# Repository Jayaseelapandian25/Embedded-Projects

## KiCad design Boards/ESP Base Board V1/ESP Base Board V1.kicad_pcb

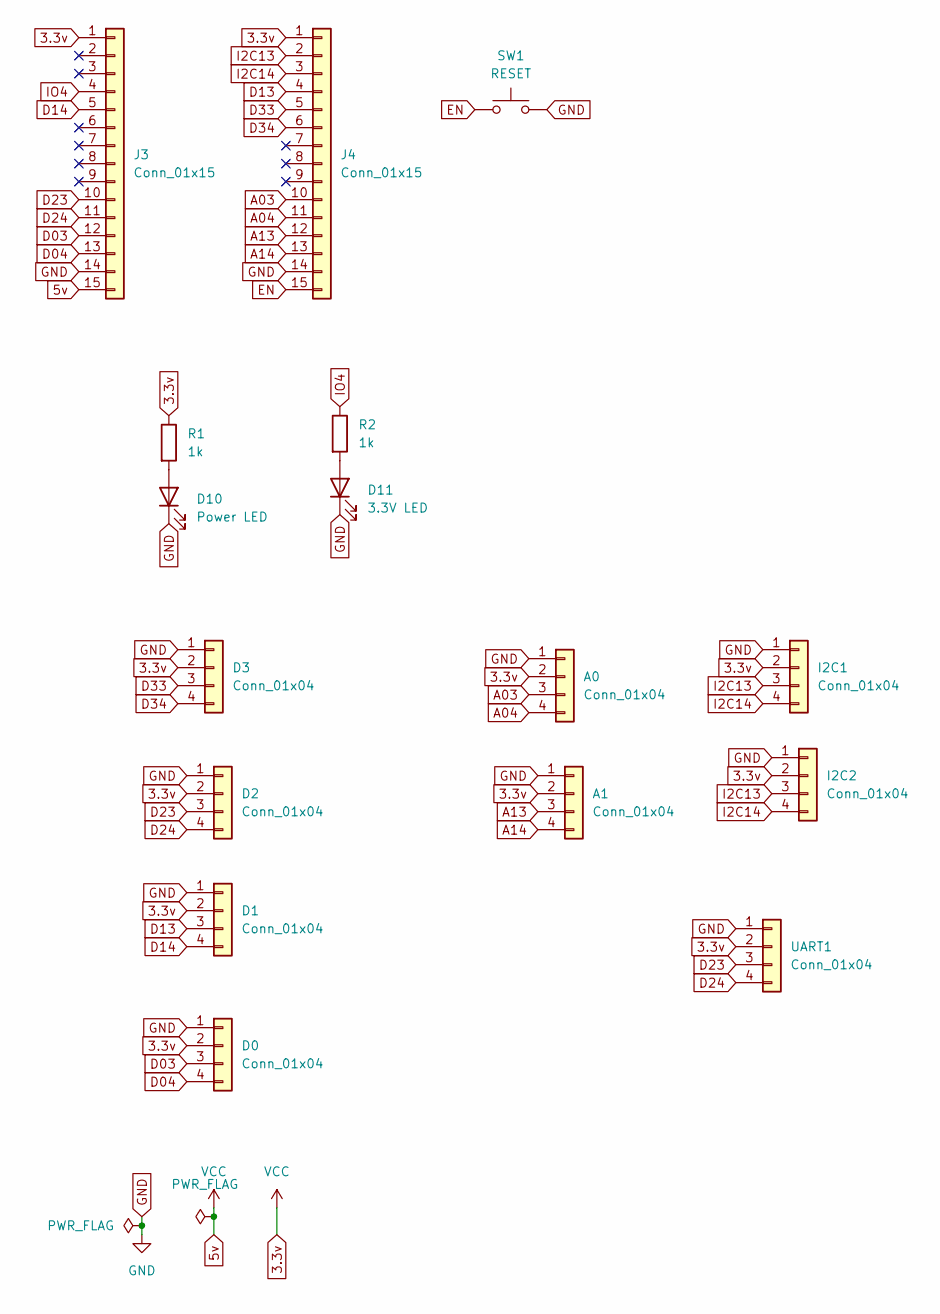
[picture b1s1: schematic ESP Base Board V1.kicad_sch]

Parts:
A0, A1: Conn_01x04; PinHeader_1x04_P2.54mm_Vertical
D0, D1, D2, D3: Conn_01x04; PinHeader_1x04_P2.54mm_Vertical
D10: Power LED; LED_0805_2012Metric_Pad1.15x1.40mm_HandSolder
D11: 3.3V LED; LED_0805_2012Metric_Pad1.15x1.40mm_HandSolder
I2C1, I2C2: Conn_01x04; PinHeader_1x04_P2.54mm_Vertical
J3, J4: Conn_01x15; PinSocket_1x15_P2.54mm_Vertical
R1, R2: 1k; R_0805_2012Metric_Pad1.20x1.40mm_HandSolder
SW1: RESET; SW_SPST_TL3342
UART1: Conn_01x04; PinHeader_1x04_P2.54mm_Vertical

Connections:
3.3v: A0.2, A1.2, D0.2, D1.2, D2.2, D3.2, I2C1.2, I2C2.2, J3.1, J3.15, J4.1, R1.1, UART1.2
A03: A0.3, J4.10
A04: A0.4, J4.11
A13: A1.3, J4.12
A14: A1.4, J4.13
D03: D0.3, J3.12
D04: D0.4, J3.13
D13: D1.3, J4.4
D14: D1.4, J3.5
D23: D2.3, J3.10, UART1.3
D24: D2.4, J3.11, UART1.4
D33: D3.3, J4.5
D34: D3.4, J4.6
EN: J4.15, SW1.1
GND: A0.1, A1.1, D0.1, D1.1, D2.1, D3.1, D10.1 (K), D11.1 (K), I2C1.1, I2C2.1, J3.14, J4.14, SW1.2, UART1.1
I2C13: I2C1.3, I2C2.3, J4.2
I2C14: I2C1.4, I2C2.4, J4.3
IO4: J3.4, R2.1
unnamed: D10.2 (A), R1.2
unnamed: D11.2 (A), R2.2

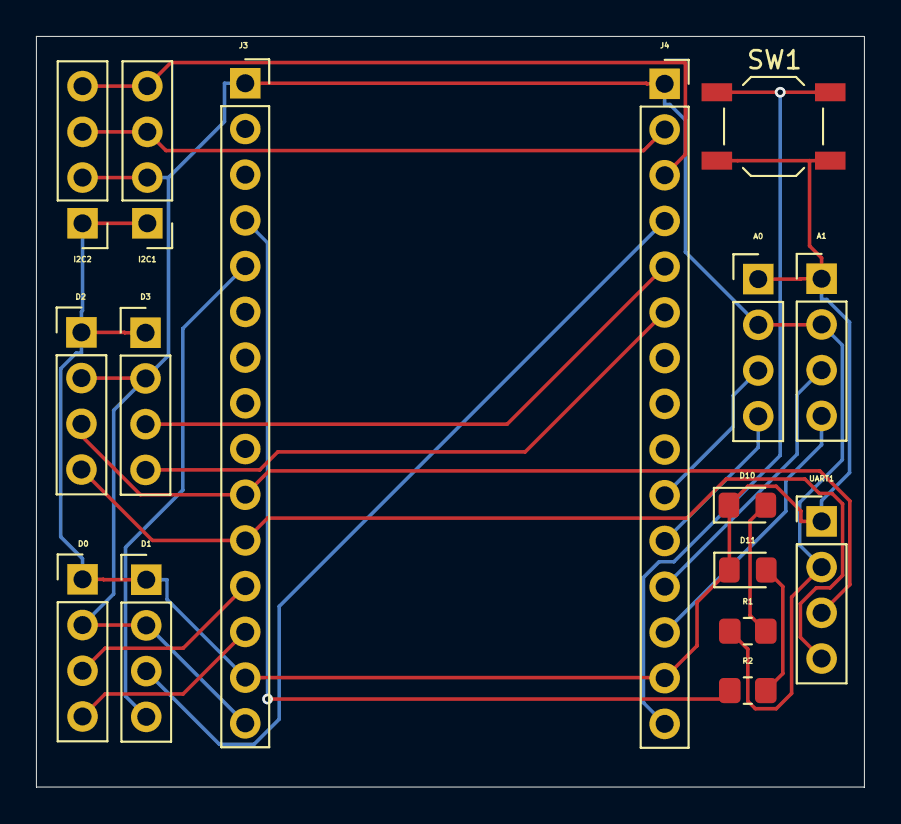
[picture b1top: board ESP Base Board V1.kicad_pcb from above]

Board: 2 copper layers, 46.0 x 41.7 mm, 16 parts (0 on the bottom side), 20 nets.

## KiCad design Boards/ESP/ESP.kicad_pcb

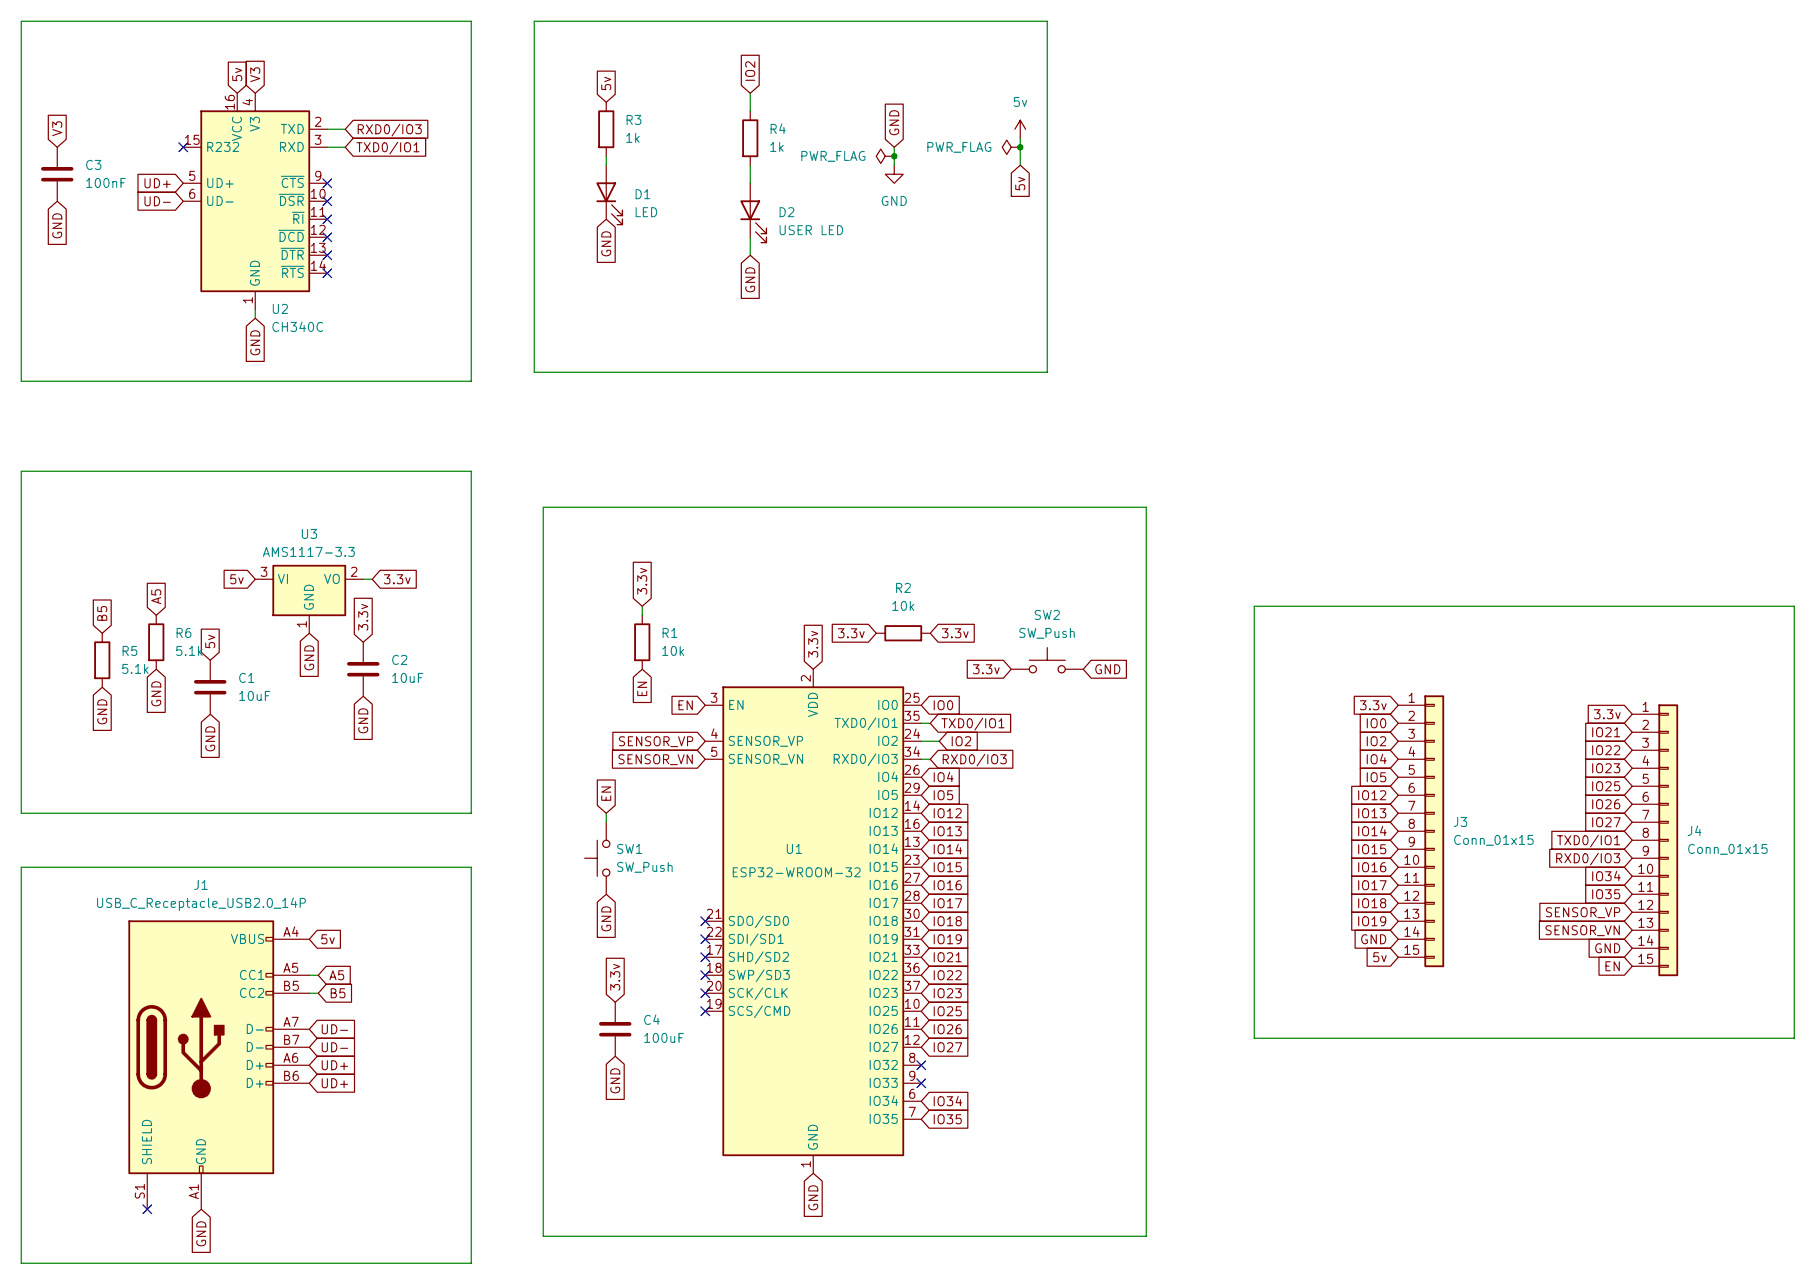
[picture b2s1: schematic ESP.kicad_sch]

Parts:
C1, C2: 10uF; C_0805_2012Metric
C3: 100nF; C_0805_2012Metric
C4: 100uF; C_0805_2012Metric
D1: LED; LED_0805_2012Metric
D2: USER LED; LED_0805_2012Metric
J1: USB_C_Receptacle_USB2.0_14P; USB_C_Receptacle_HRO_TYPE-C-31-M-12
J3, J4: Conn_01x15; PinHeader_1x15_P2.54mm_Vertical
R1, R2: 10k; R_0805_2012Metric
R3, R4: 1k; R_0805_2012Metric
R5, R6: 5.1k; R_0805_2012Metric
SW1, SW2: SW_Push; SW_SPST_TL3342
U1: ESP32-WROOM-32
U2: CH340C; SOIC-16_3.9x9.9mm_P1.27mm
U3: AMS1117-3.3; SOT-223-3_TabPin2

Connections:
3.3v: C2.1, C4.1, J3.1, J4.1, R1.1, R2.1, R2.2, SW2.1, U1.2 (VDD), U3.2 (VO)
5v: C1.1, J1.A4 (VBUS), J1.A9 (VBUS), J1.B4 (VBUS), J1.B9 (VBUS), J3.15, R3.1, U2.16 (VCC), U3.3 (VI)
A5: J1.A5 (CC1), R6.1
B5: J1.B5 (CC2), R5.1
EN: J4.15, R1.2, SW1.2, U1.3 (EN)
GND: C1.2, C2.2, C3.2, C4.2, D1.1 (K), D2.1 (K), J1.A1 (GND), J1.A12 (GND), J1.B1 (GND), J1.B12 (GND), J3.14, J4.14, R5.2, R6.2, SW1.1, SW2.2, U1.1 (GND), U1.15 (GND), U1.38 (GND), U1.39 (GND), U2.1 (GND), U3.1 (GND)
IO0: J3.2, U1.25 (IO0)
IO2: J3.3, R4.1, U1.24 (IO2)
IO4: J3.4, U1.26 (IO4)
IO5: J3.5, U1.29 (IO5)
IO12: J3.6, U1.14 (IO12)
IO13: J3.7, U1.16 (IO13)
IO14: J3.8, U1.13 (IO14)
IO15: J3.9, U1.23 (IO15)
IO16: J3.10, U1.27 (IO16)
IO17: J3.11, U1.28 (IO17)
IO18: J3.12, U1.30 (IO18)
IO19: J3.13, U1.31 (IO19)
IO21: J4.2, U1.33 (IO21)
IO22: J4.3, U1.36 (IO22)
IO23: J4.4, U1.37 (IO23)
IO25: J4.5, U1.10 (IO25)
IO26: J4.6, U1.11 (IO26)
IO27: J4.7, U1.12 (IO27)
IO34: J4.10, U1.6 (IO34)
IO35: J4.11, U1.7 (IO35)
unnamed: D1.2 (A), R3.2
unnamed: D2.2 (A), R4.2
RXD0/IO3: J4.9, U1.34 (RXD0/IO3), U2.2 (TXD)
SENSOR_VN: J4.13, U1.5 (SENSOR_VN)
SENSOR_VP: J4.12, U1.4 (SENSOR_VP)
TXD0/IO1: J4.8, U1.35 (TXD0/IO1), U2.3 (RXD)
UD+: J1.A6 (D+), J1.B6 (D+), U2.5 (UD+)
UD-: J1.A7 (D-), J1.B7 (D-), U2.6 (UD-)
V3: C3.1, U2.4 (V3)

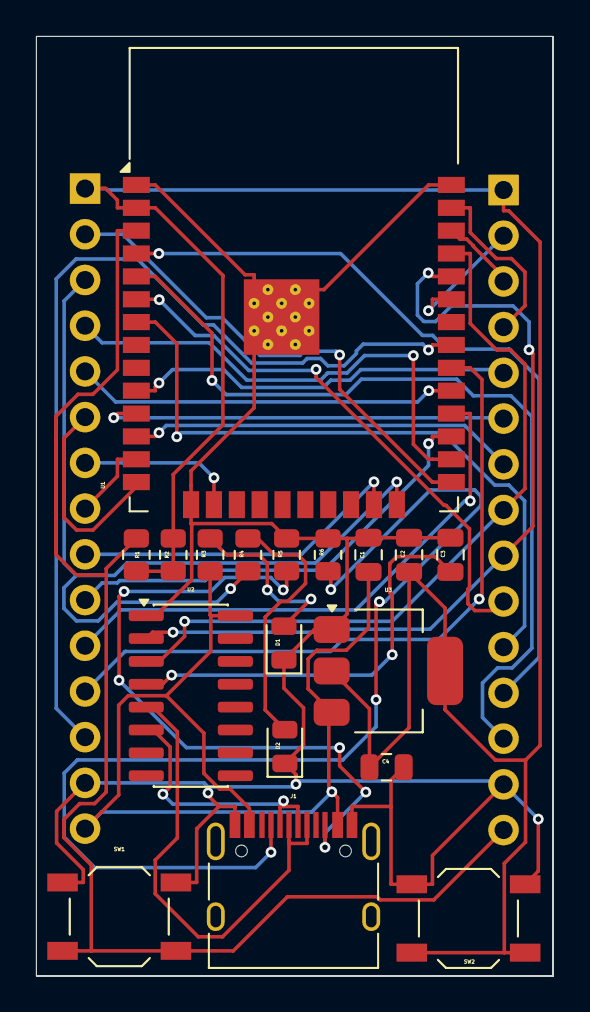
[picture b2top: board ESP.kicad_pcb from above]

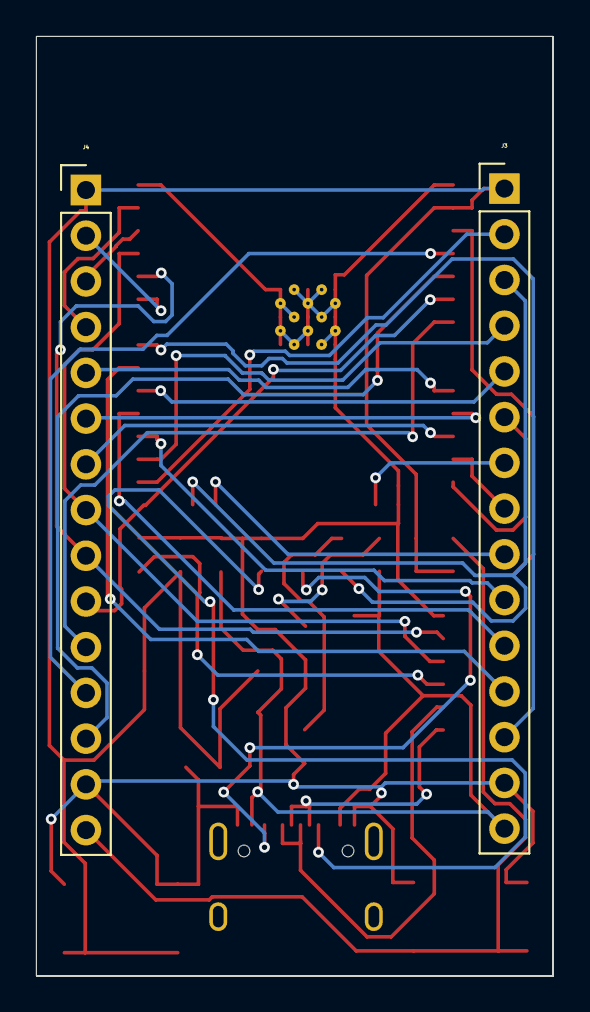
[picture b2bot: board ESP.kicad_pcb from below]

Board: 2 copper layers, 28.7 x 52.2 mm, 20 parts (2 on the bottom side), 35 nets.

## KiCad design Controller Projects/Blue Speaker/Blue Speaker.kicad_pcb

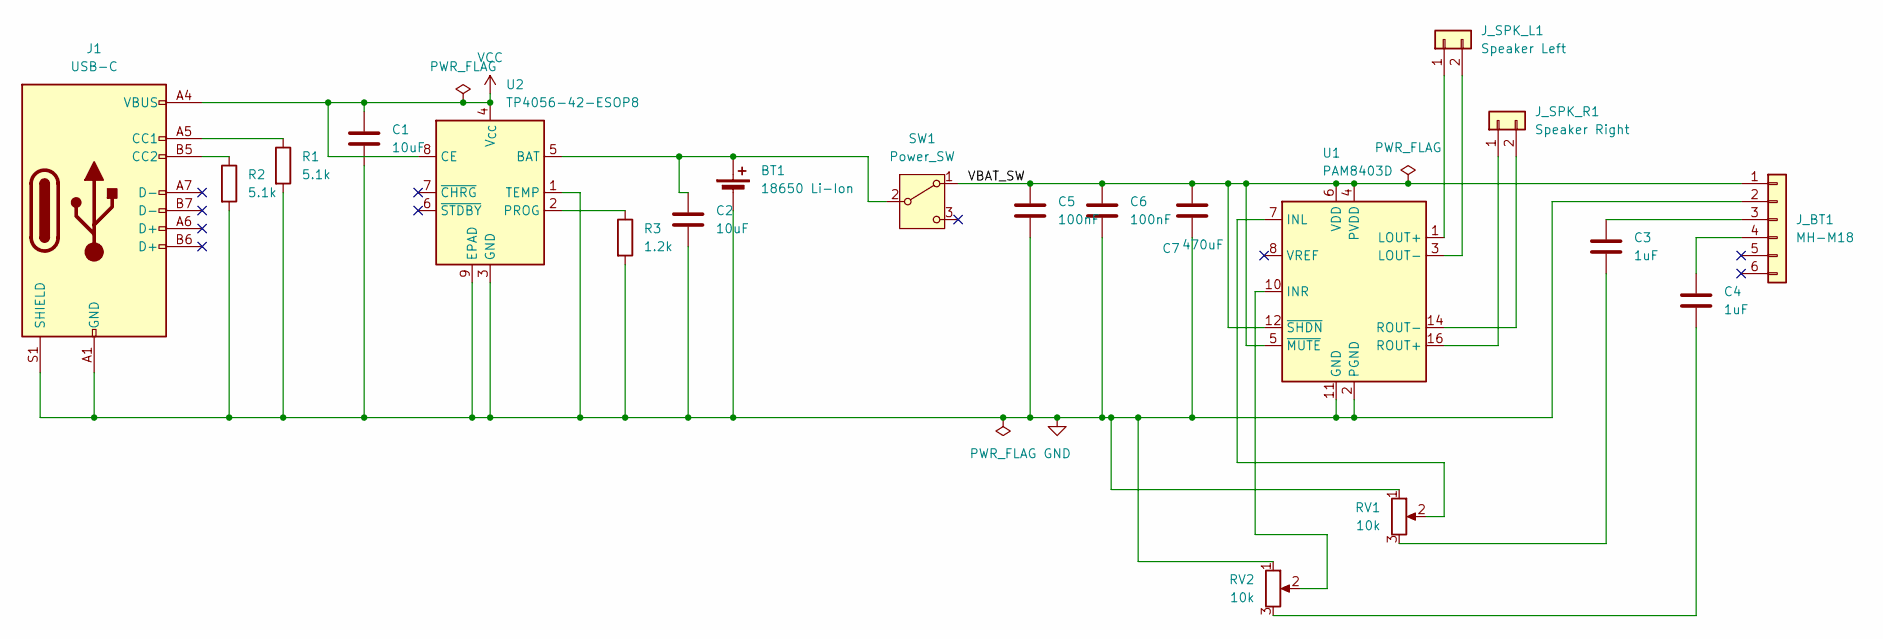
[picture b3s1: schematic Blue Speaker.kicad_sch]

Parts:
BT1: 18650 Li-Ion; PinHeader_1x02_P2.54mm_Vertical
C1, C2: 10uF; C_0805_2012Metric_Pad1.18x1.45mm_HandSolder
C3, C4: 1uF; C_0805_2012Metric_Pad1.18x1.45mm_HandSolder
C5, C6: 100nF; C_0805_2012Metric_Pad1.18x1.45mm_HandSolder
C7: 470uF; CP_Elec_6.3x5.4
J1: USB-C; USB_C_Receptacle_HRO_TYPE-C-31-M-12
J_BT1: MH-M18; PinSocket_1x06_P2.54mm_Vertical
J_SPK_L1: Speaker Left; PinHeader_1x02_P2.54mm_Vertical
J_SPK_R1: Speaker Right; PinHeader_1x02_P2.54mm_Vertical
R1, R2: 5.1k; R_0805_2012Metric_Pad1.20x1.40mm_HandSolder
R3: 1.2k; R_0805_2012Metric_Pad1.20x1.40mm_HandSolder
RV1, RV2: 10k; Potentiometer_Bourns_3296W_Vertical
SW1: Power_SW; SW_E-Switch_EG1224_SPDT_Angled
U1: PAM8403D; SOIC-16_3.9x9.9mm_P1.27mm
U2: TP4056-42-ESOP8; SOIC-8-1EP_3.9x4.9mm_P1.27mm_EP2.41x3.3mm_ThermalVias

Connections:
/VBAT_SW: C5.1, C6.1, C7.1, J_BT1.1, SW1.1 (A), U1.4 (PVDD), U1.5 (~MUTE), U1.6 (VDD), U1.12 (~SHDN), U1.13 (PVDD)
GND: BT1.2 (-), C1.2, C2.2, C5.2, C6.2, C7.2, J1.A1 (GND), J1.A12 (GND), J1.B1 (GND), J1.B12 (GND), J1.S1 (SHIELD), J_BT1.2, R1.2, R2.2, R3.2, RV1.1, RV2.1, U1.2 (PGND), U1.11 (GND), U1.15 (PGND), U2.1 (TEMP), U2.3 (GND), U2.9 (EPAD)
unnamed: BT1.1 (+), C2.1, SW1.2 (B), U2.5 (BAT)
unnamed: C3.2, RV1.3
unnamed: C4.2, RV2.3
unnamed: J1.A5 (CC1), R1.1
unnamed: J1.B5 (CC2), R2.1
unnamed: C3.1, J_BT1.3
unnamed: C4.1, J_BT1.4
unnamed: J_SPK_L1.1, U1.1 (LOUT+)
unnamed: J_SPK_L1.2, U1.3 (LOUT-)
unnamed: J_SPK_R1.1, U1.16 (ROUT+)
unnamed: J_SPK_R1.2, U1.14 (ROUT-)
unnamed: RV1.2, U1.7 (INL)
unnamed: RV2.2, U1.10 (INR)
unnamed: R3.1, U2.2 (PROG)
VCC: C1.1, J1.A4 (VBUS), J1.A9 (VBUS), J1.B4 (VBUS), J1.B9 (VBUS), U2.4 (V_{CC}), U2.8 (CE)

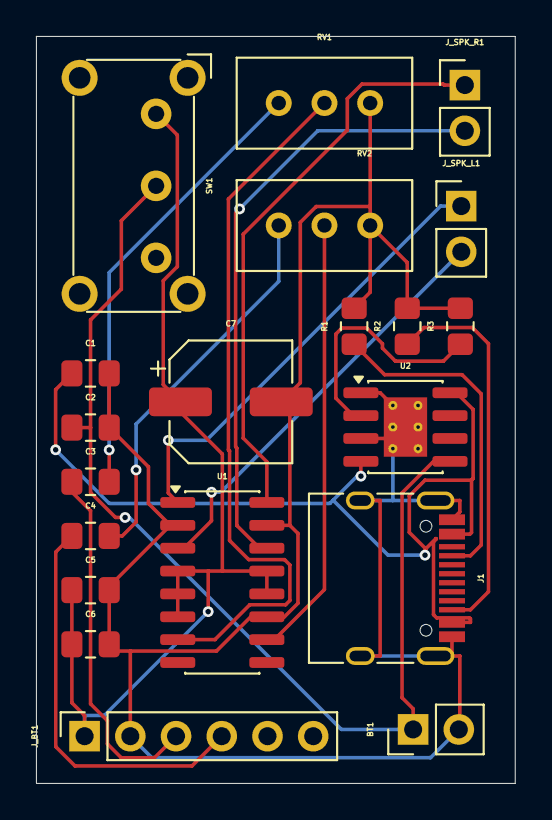
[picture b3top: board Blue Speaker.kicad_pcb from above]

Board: 2 copper layers, 26.6 x 41.5 mm, 20 parts (0 on the bottom side), 17 nets.

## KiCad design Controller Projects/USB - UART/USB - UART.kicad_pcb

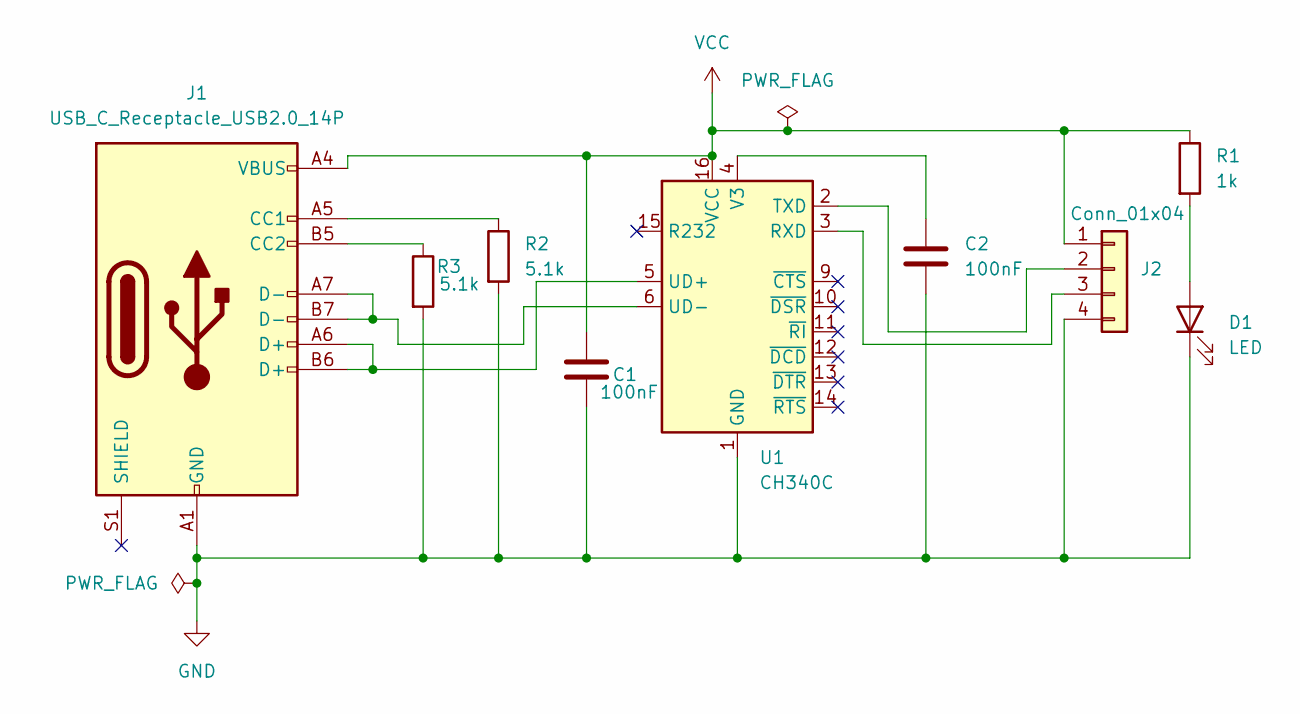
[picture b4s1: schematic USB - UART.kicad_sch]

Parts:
C1, C2: 100nF; C_0805_2012Metric_Pad1.18x1.45mm_HandSolder
D1: LED; LED_0805_2012Metric_Pad1.15x1.40mm_HandSolder
J1: USB_C_Receptacle_USB2.0_14P; USB_C_Receptacle_HRO_TYPE-C-31-M-12
J2: Conn_01x04; PinHeader_1x04_P2.54mm_Vertical
R1: 1k; R_0805_2012Metric_Pad1.20x1.40mm_HandSolder
R2, R3: 5.1k; R_0805_2012Metric_Pad1.20x1.40mm_HandSolder
U1: CH340C; SOIC-16_3.9x9.9mm_P1.27mm

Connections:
GND: C1.2, C2.2, D1.1 (K), J1.A1 (GND), J1.A12 (GND), J1.B1 (GND), J1.B12 (GND), J2.4, R2.2, R3.2, U1.1 (GND)
unnamed: D1.2 (A), R1.2
unnamed: J1.A5 (CC1), R2.1
unnamed: J1.B5 (CC2), R3.1
unnamed: J2.2, U1.2 (TXD)
unnamed: J2.3, U1.3 (RXD)
unnamed: J1.A6 (D+), J1.B6 (D+), U1.5 (UD+)
unnamed: J1.A7 (D-), J1.B7 (D-), U1.6 (UD-)
unnamed: C2.1, U1.4 (V3)
VCC: C1.1, J1.A4 (VBUS), J1.A9 (VBUS), J1.B4 (VBUS), J1.B9 (VBUS), J2.1, R1.1, U1.16 (VCC)

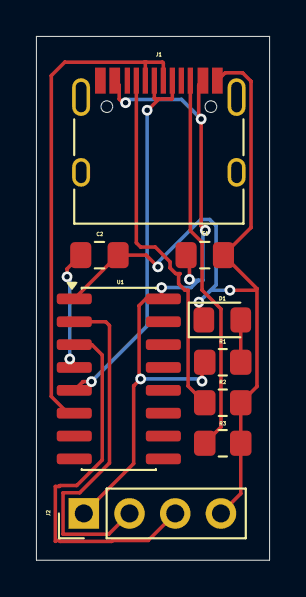
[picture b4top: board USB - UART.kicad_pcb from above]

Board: 2 copper layers, 12.9 x 29.1 mm, 9 parts (0 on the bottom side), 10 nets.

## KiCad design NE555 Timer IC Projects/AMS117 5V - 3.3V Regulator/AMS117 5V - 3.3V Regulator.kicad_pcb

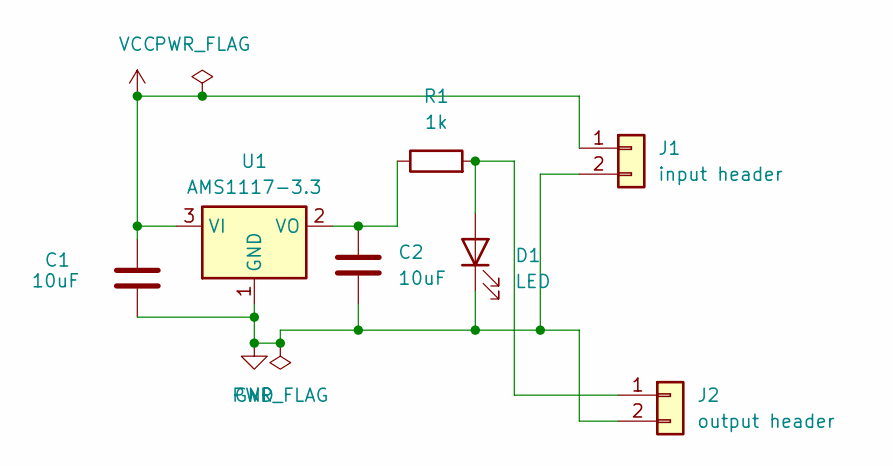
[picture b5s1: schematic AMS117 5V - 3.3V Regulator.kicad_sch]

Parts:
C1, C2: 10uF; C_0805_2012Metric_Pad1.18x1.45mm_HandSolder
D1: LED; LED_0805_2012Metric_Pad1.15x1.40mm_HandSolder
J1: input header; PinHeader_1x02_P2.54mm_Vertical
J2: output header; PinHeader_1x02_P2.54mm_Vertical
R1: 1k; R_0805_2012Metric_Pad1.20x1.40mm_HandSolder
U1: AMS1117-3.3; SOT-223-3_TabPin2

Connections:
GND: C1.2, C2.2, D1.1 (K), J1.2, J2.2, U1.1 (GND)
unnamed: D1.2 (A), J2.1, R1.2
unnamed: C2.1, R1.1, U1.2 (VO)
VCC: C1.1, J1.1, U1.3 (VI)

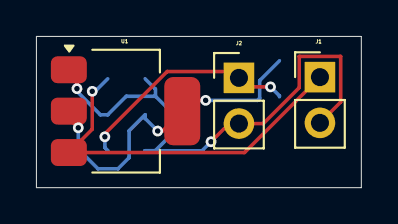
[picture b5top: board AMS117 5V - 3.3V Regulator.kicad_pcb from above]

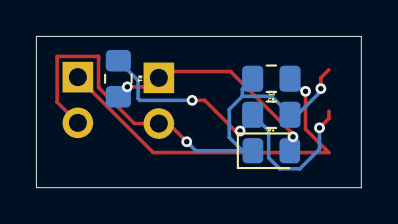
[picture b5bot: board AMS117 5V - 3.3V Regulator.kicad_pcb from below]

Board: 2 copper layers, 18.0 x 8.4 mm, 7 parts (4 on the bottom side), 4 nets.

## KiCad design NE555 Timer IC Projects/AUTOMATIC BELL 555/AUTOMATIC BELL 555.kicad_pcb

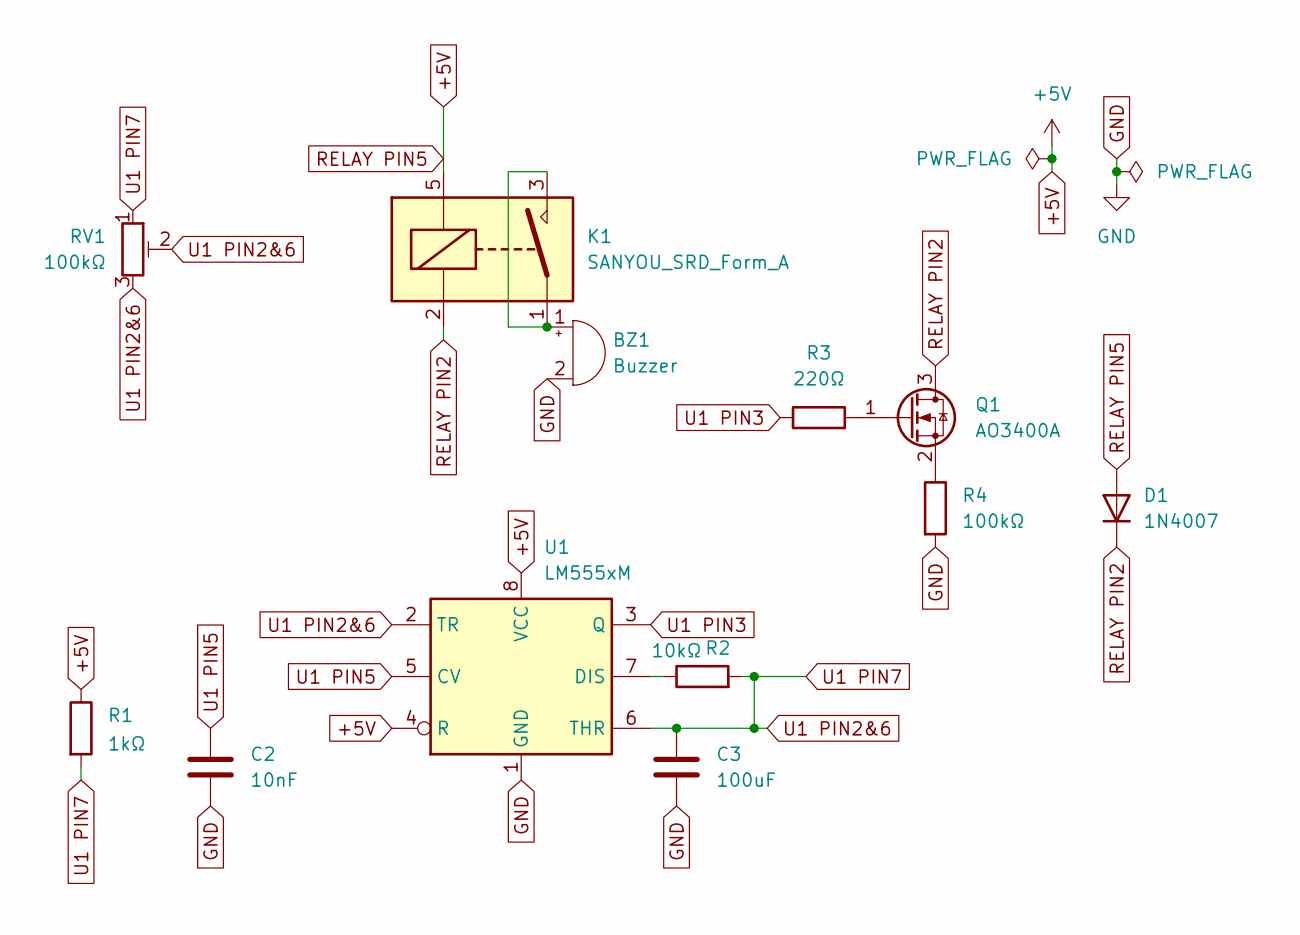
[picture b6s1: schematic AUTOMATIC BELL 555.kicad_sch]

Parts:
BZ1: Buzzer; Buzzer_12x9.5RM7.6
C2: 10nF; C_0805_2012Metric
C3: 100uF; C_0805_2012Metric
D1: 1N4007; D_SMA
K1: SANYOU_SRD_Form_A; Relay_SPST_SANYOU_SRD_Series_Form_A
Q1: AO3400A; SOT-23
R1: 1kΩ; R_0805_2012Metric
R2: 10kΩ; R_0805_2012Metric
R3: 220Ω; R_0805_2012Metric
R4: 100kΩ; R_0805_2012Metric
RV1: 100kΩ; Potentiometer_Bourns_3296W_Vertical
U1: LM555xM; SOIC-8_3.9x4.9mm_P1.27mm

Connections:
+5V: D1.2 (A), K1.5, R1.1, U1.4 (R), U1.8 (VCC)
GND: BZ1.2 (-), C2.2, C3.2, R4.2, U1.1 (GND)
unnamed: BZ1.1 (+), K1.1, K1.3
unnamed: Q1.1 (G), R3.2
unnamed: Q1.2 (S), R4.1
unnamed: R2.1, U1.7 (DIS)
RELAY PIN2: D1.1 (K), K1.2, Q1.3 (D)
U1 PIN2&6: C3.1, R1.2, R2.2, RV1.1, RV1.2, RV1.3, U1.2 (TR), U1.6 (THR)
U1 PIN3: R3.1, U1.3 (Q)
U1 PIN5: C2.1, U1.5 (CV)

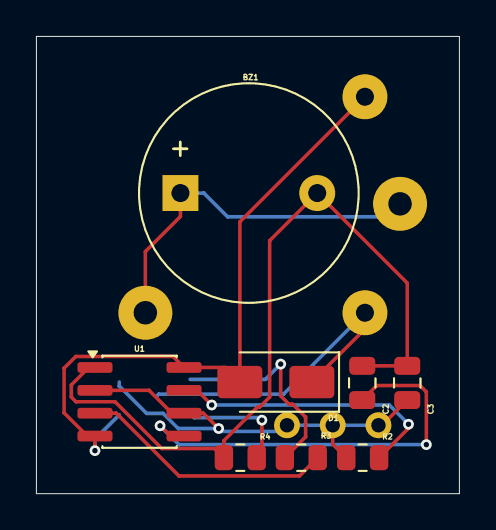
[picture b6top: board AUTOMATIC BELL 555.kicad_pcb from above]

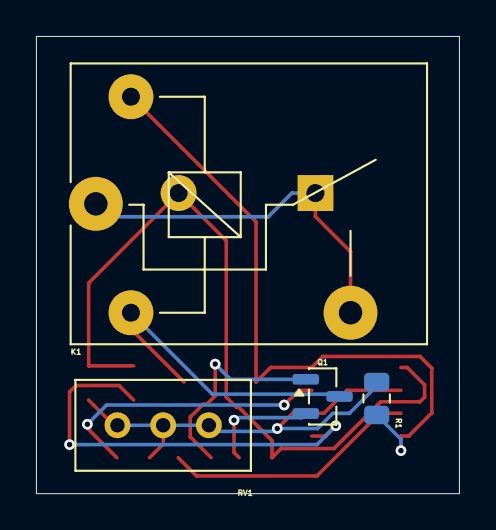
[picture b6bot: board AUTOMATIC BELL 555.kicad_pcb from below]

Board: 2 copper layers, 23.5 x 25.4 mm, 12 parts (4 on the bottom side), 10 nets.

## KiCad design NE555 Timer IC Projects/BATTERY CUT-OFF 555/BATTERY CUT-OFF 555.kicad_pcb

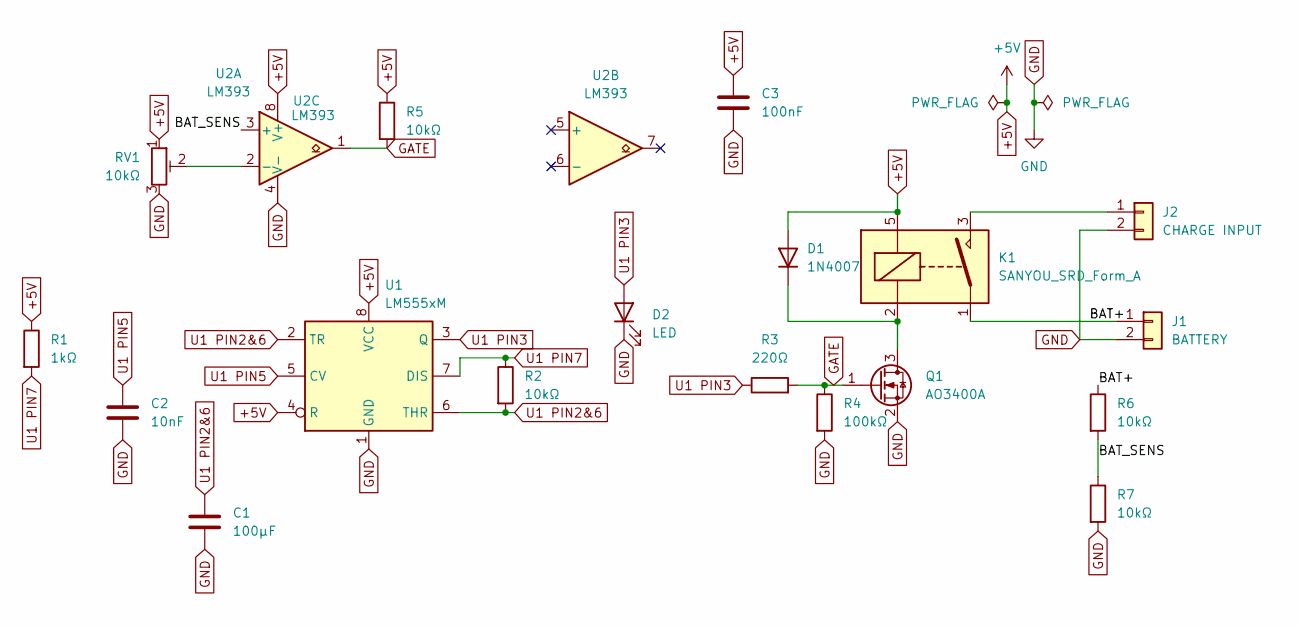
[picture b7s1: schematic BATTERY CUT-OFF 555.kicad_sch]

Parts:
C1: 100µF; C_0805_2012Metric
C2: 10nF; C_0805_2012Metric
C3: 100nF; C_0805_2012Metric
D1: 1N4007; D_SMA
D2: LED; LED_0805_2012Metric
J1: BATTERY; JST_PH_B2B-PH-K_1x02_P2.00mm_Vertical
J2: CHARGE INPUT; JST_PH_B2B-PH-K_1x02_P2.00mm_Vertical
K1: SANYOU_SRD_Form_A; Relay_SPST_SANYOU_SRD_Series_Form_A
Q1: AO3400A; SOT-23
R1: 1kΩ; R_0805_2012Metric
R2, R5, R6, R7: 10kΩ; R_0805_2012Metric
R3: 220Ω; R_0805_2012Metric
R4: 100kΩ; R_0805_2012Metric
RV1: 10kΩ; Potentiometer_Bourns_3296W_Vertical
U1: LM555xM; SOIC-8_3.9x4.9mm_P1.27mm
U2: LM393; SOIC-8_3.9x4.9mm_P1.27mm

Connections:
+5V: C3.1, D1.2 (A), K1.5, R1.1, R5.1, RV1.1, U1.4 (R), U1.8 (VCC), U2.8 (V+)
/BAT+: J1.1, K1.1, R6.1
/BAT_SENS: R6.2, R7.1, U2.3 (+)
GATE: Q1.1 (G), R3.2, R4.1, R5.2, U2.1
GND: C1.2, C2.2, C3.2, D2.1 (K), J1.2, J2.2, Q1.2 (S), R4.2, R7.2, RV1.3, U1.1 (GND), U2.4 (V-)
unnamed: D1.1 (K), K1.2, Q1.3 (D)
unnamed: J2.1, K1.3
unnamed: RV1.2, U2.2 (-)
U1 PIN2&6: C1.1, R2.2, U1.2 (TR), U1.6 (THR)
U1 PIN3: D2.2 (A), R3.1, U1.3 (Q)
U1 PIN5: C2.1, U1.5 (CV)
U1 PIN7: R1.2, R2.1, U1.7 (DIS)

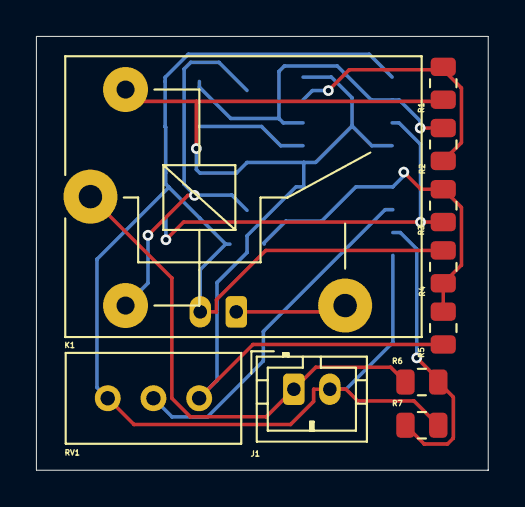
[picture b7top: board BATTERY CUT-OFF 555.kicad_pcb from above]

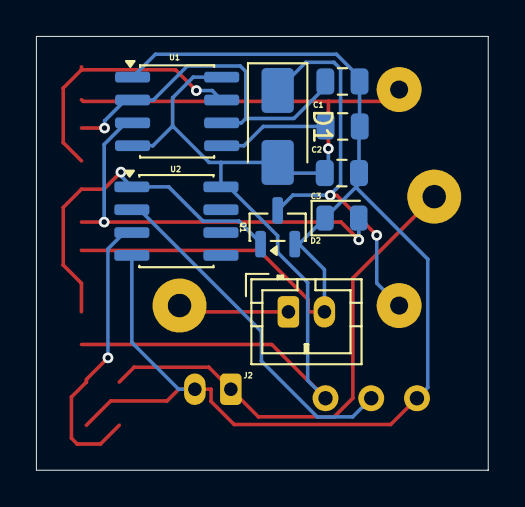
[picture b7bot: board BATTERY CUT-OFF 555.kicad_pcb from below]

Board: 2 copper layers, 25.1 x 24.1 mm, 19 parts (9 on the bottom side), 12 nets.

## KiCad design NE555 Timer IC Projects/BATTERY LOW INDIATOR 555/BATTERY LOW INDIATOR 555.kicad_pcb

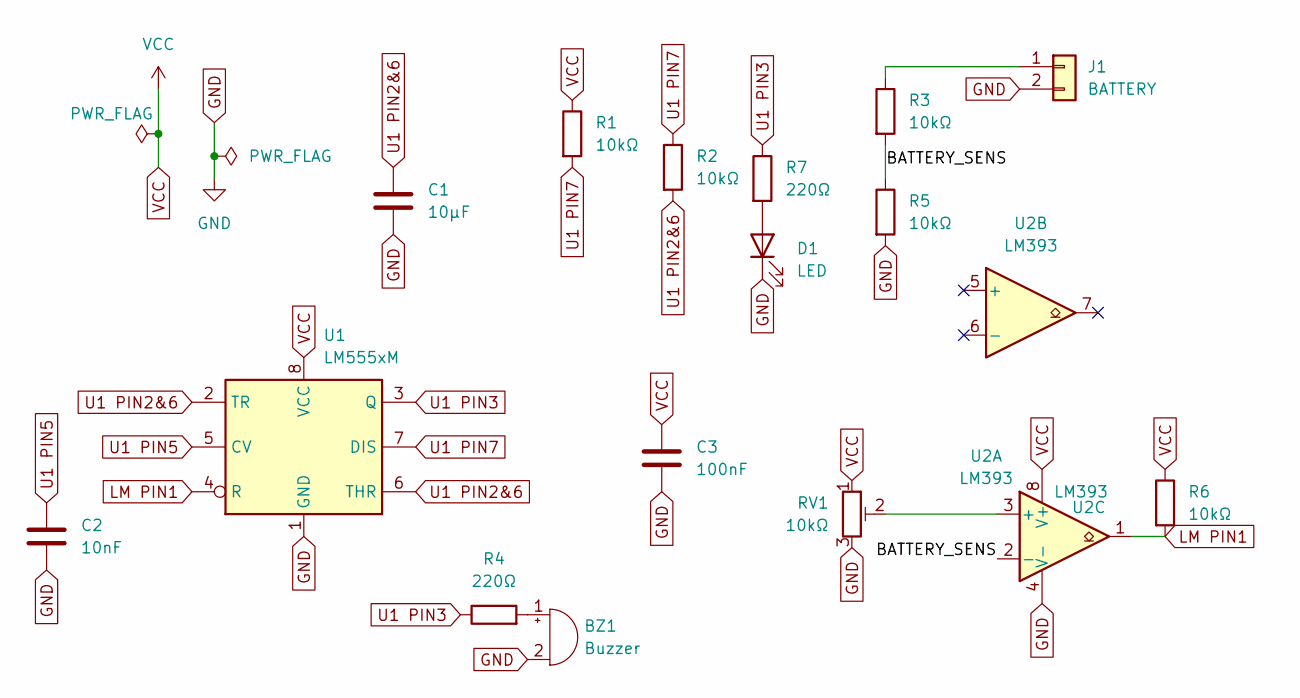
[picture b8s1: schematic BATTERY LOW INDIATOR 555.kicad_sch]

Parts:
BZ1: Buzzer; Buzzer_12x9.5RM7.6
C1: 10µF; C_0805_2012Metric
C2: 10nF; C_0805_2012Metric
C3: 100nF; C_0805_2012Metric
D1: LED; LED_0805_2012Metric_Pad1.15x1.40mm_HandSolder
J1: BATTERY; JST_PH_B2B-PH-K_1x02_P2.00mm_Vertical
R1, R2, R3, R5, R6: 10kΩ; R_0805_2012Metric
R4, R7: 220Ω; R_0805_2012Metric
RV1: 10kΩ; Potentiometer_Bourns_3296W_Vertical
U1: LM555xM; SOIC-8_3.9x4.9mm_P1.27mm
U2: LM393; SOIC-8_3.9x4.9mm_P1.27mm

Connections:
/BATTERY_SENS: R3.2, R5.1, U2.2 (-)
GND: BZ1.2 (-), C1.2, C2.2, C3.2, D1.1 (K), J1.2, R5.2, RV1.3, U1.1 (GND), U2.4 (V-)
LM PIN1: R6.2, U1.4 (R), U2.1
unnamed: BZ1.1 (+), R4.2
unnamed: D1.2 (A), R7.2
unnamed: J1.1, R3.1
unnamed: RV1.2, U2.3 (+)
U1 PIN2&6: C1.1, R2.2, U1.2 (TR), U1.6 (THR)
U1 PIN3: R4.1, R7.1, U1.3 (Q)
U1 PIN5: C2.1, U1.5 (CV)
U1 PIN7: R1.2, R2.1, U1.7 (DIS)
VCC: C3.1, R1.1, R6.1, RV1.1, U1.8 (VCC), U2.8 (V+)
